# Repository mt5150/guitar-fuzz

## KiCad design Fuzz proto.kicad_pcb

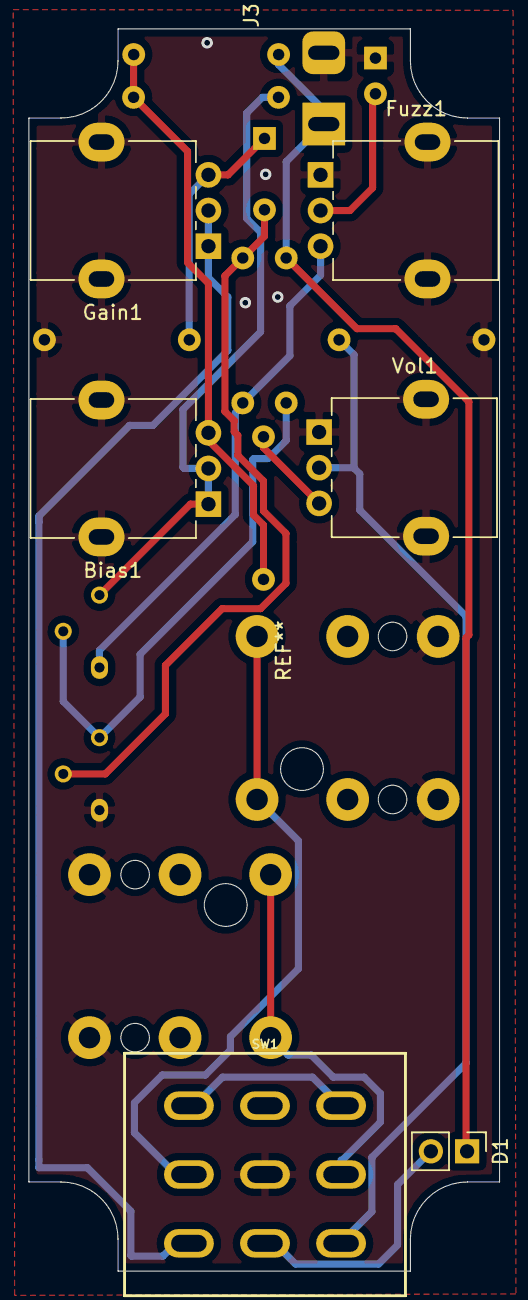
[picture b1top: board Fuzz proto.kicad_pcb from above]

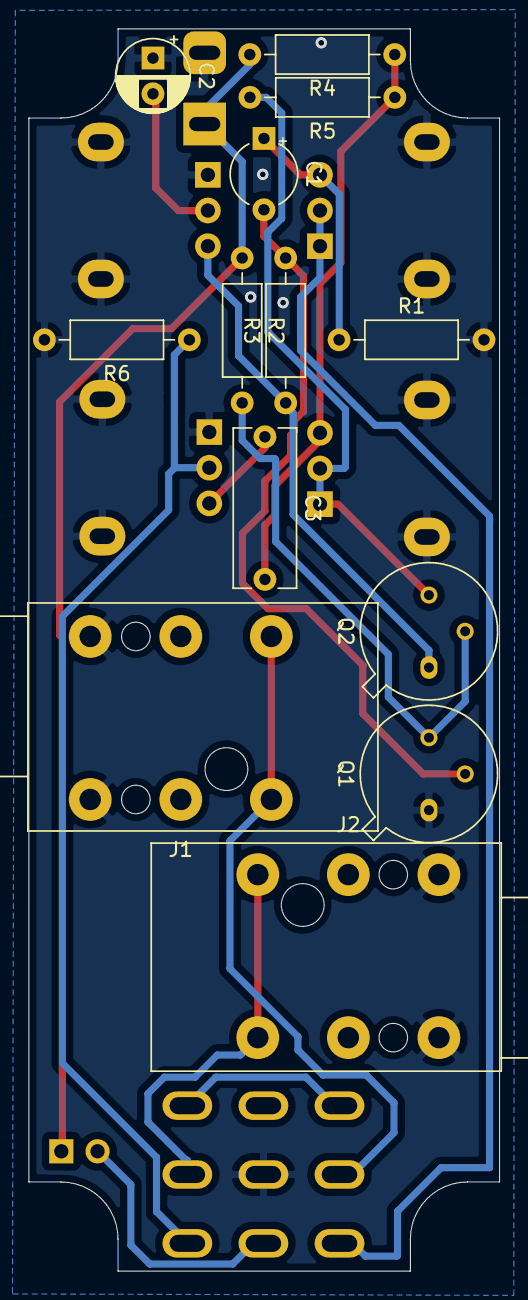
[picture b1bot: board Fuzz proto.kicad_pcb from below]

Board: 2 copper layers, 33.0 x 87.1 mm, 20 parts (13 on the bottom side), 16 nets.

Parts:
Bias1: 10k; Potentiometer_Alpha_RD901F-40-00D_Single_Vertical
C1: 2,2uF; CP_Radial_Tantal_D4.5mm_P5.00mm
C2: 22uF; CP_Radial_D5.0mm_P2.50mm
C3: 10nF; C_Rect_L11.0mm_W4.2mm_P10.00mm_MKT
D1: LED; PinHeader_1x02_P2.54mm_Vertical
Fuzz1: B1k; Potentiometer_Alpha_RD901F-40-00D_Single_Vertical
Gain1: B100k; Potentiometer_Alpha_RD901F-40-00D_Single_Vertical
J1: IN; Jack_6.35mm_Neutrik_NRJ6HF-1_Horizontal
J2: OUT; Jack_6.35mm_Neutrik_NRJ6HF-1_Horizontal
J3: DC IN; BarrelJack_Vertical
Q1, Q2: Q_PNP_BCE; TO-5-3
R1: 1M; R_Axial_DIN0207_L6.3mm_D2.5mm_P10.16mm_Horizontal
R2: 33k; R_Axial_DIN0207_L6.3mm_D2.5mm_P10.16mm_Horizontal
R3, R6: 100k; R_Axial_DIN0207_L6.3mm_D2.5mm_P10.16mm_Horizontal
R4: 330; R_Axial_DIN0207_L6.3mm_D2.5mm_P10.16mm_Horizontal
R5: 8,2k; R_Axial_DIN0207_L6.3mm_D2.5mm_P10.16mm_Horizontal
SW1: SW_3PDT; STOMP_SWITCH_3PDT_connectors
Vol1: A500k; Potentiometer_Alpha_RD901F-40-00D_Single_Vertical

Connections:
EFX_IN: Gain1.1, Gain1.2, SW1.3
EFX_OUT: R6.1, SW1.9, Vol1.2
GND: C2.1, Fuzz1.1, J1.G, J1.S, J2.G, J2.S, J3.2, Q1.1, R1.2, R6.2, SW1.5, Vol1.1
IN: J1.T, J1.TN, SW1.2
LED-: D1.2, SW1.6
unnamed: Bias1.1, Bias1.2, Q2.3, R5.2
unnamed: Bias1.3, C3.2, R4.1, R5.1
unnamed: C1.1, Gain1.3, R1.1
unnamed: C1.2, Q1.2, R3.2
unnamed: C2.2, Fuzz1.2
unnamed: C3.1, Vol1.3
unnamed: D1.1, J3.1, R2.1, R4.2
unnamed: Fuzz1.3, Q2.1, R3.1
unnamed: Q1.3, Q2.2, R2.2
unnamed: SW1.1, SW1.7
OUT: J2.T, J2.TN, SW1.8

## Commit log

2023-06-05 init
2023-06-05 Tidied up project. Added docs and pics.
